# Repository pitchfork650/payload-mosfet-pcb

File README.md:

## backup-payload

# Welcome to the 2027 backup payload team!  

# Competition Objective:  
We need to drop a 3lb (1.36kg), 11in x 9in x 4in (280mm x 230mm x 102mm) object from a height of >=150ft above the ground within a 100ft diameter circle on the ground.  

The object must land intact and cannot free-fall!

# Design Priorities:

1: Reliability and Simplicity - This is the fallback plan and cannot fail!  
2: Aerodynamics - We cannot add excessive drag to the airframe.  
3: Weight - We are trying to stay under a total airframe weight of 18lb (8.16kg).  
4: Power - We cannot draw excessive amounts of power for our system.  

# Current Design:

We are going for a design based on a jet fighter drop tank design, with a blunter tip as we are not traveling supersonic.

- Electromagnetic release system (energize to release)
- Parachute retardant mechanism
- Completely unguided

# Documentation, Communication, and Files

We will keep as much documentation as possible in this Github, once we figure out how to use it.

Primary communication regarding meetings (not meeting notes) will be in the #backup-payload Discord channel in the TritonUAS Discord. 

- If you are having trouble finding the channel, go to your settings for the TritonUAS Discord server and find the "Show All Channels" toggle, and toggle it on.
- The channel is under the Electrical channel category.

Onshape document for all unguided payload models:
https://cad.onshape.com/documents/280ab2b1f08f9e136f51cc77/w/917fb5350924a7544787e597/e/dabe9ec72733b0c074b43efb?renderMode=0&uiState=6aeeb632a85a72a918cc2794 

Google document meeting notes (we are moving away from this ASAP): 
https://docs.google.com/document/d/1v5xJ7Shg4Nnc_SfwMuAoo-l7Iq7nKODf18gR5z6Hjh0/edit?usp=sharing
<!--
Gavin why

-->

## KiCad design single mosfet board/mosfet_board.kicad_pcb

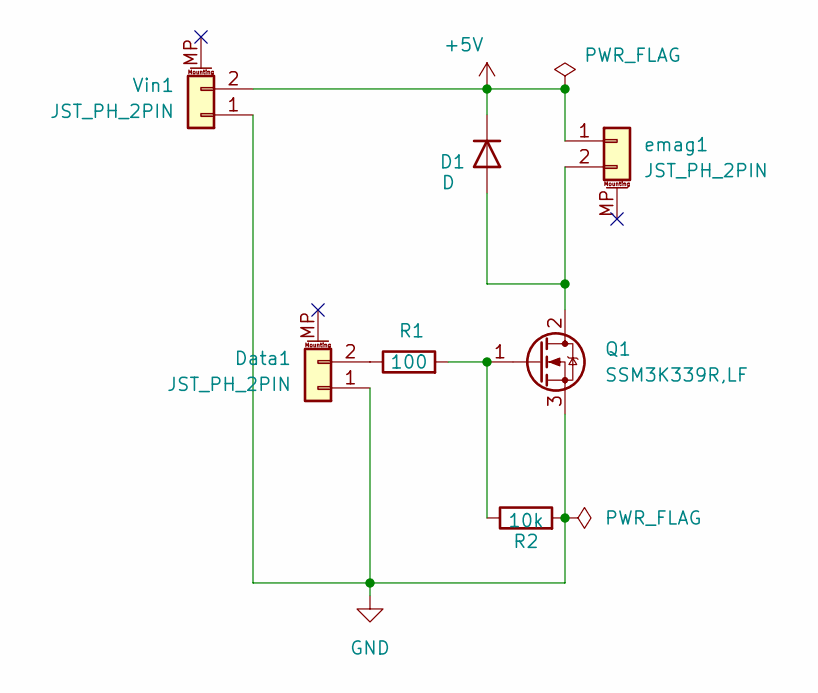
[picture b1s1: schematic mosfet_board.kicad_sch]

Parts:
D1: D; D_SOD-123
Data1: JST_PH_2PIN; JST_PH_S2B-PH-SM4-TB_1x02-1MP_P2.00mm_Horizontal
Q1: SSM3K339R,LF; SOT-23_Handsoldering
R1: 100; R_0603_1608Metric_Pad0.98x0.95mm_HandSolder
R2: 10k; R_0603_1608Metric_Pad0.98x0.95mm_HandSolder
Vin1: JST_PH_2PIN; JST_PH_S2B-PH-SM4-TB_1x02-1MP_P2.00mm_Horizontal
emag1: JST_PH_2PIN; JST_PH_S2B-PH-SM4-TB_1x02-1MP_P2.00mm_Horizontal

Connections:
+5V: D1.1 (K), Vin1.2, emag1.1
GND: Data1.1, Q1.3 (S), R2.2, Vin1.1
unnamed: D1.2 (A), Q1.2 (D), emag1.2
unnamed: Data1.2, R1.1
unnamed: Q1.1 (G), R1.2, R2.1

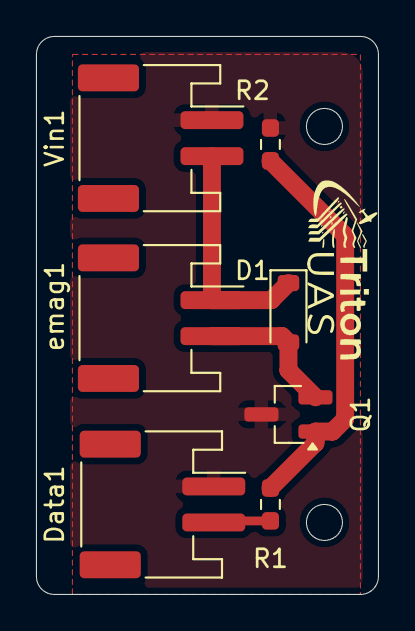
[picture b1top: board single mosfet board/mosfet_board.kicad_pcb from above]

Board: 2 copper layers, 19.0 x 31.0 mm, 7 parts (0 on the bottom side), 5 nets.

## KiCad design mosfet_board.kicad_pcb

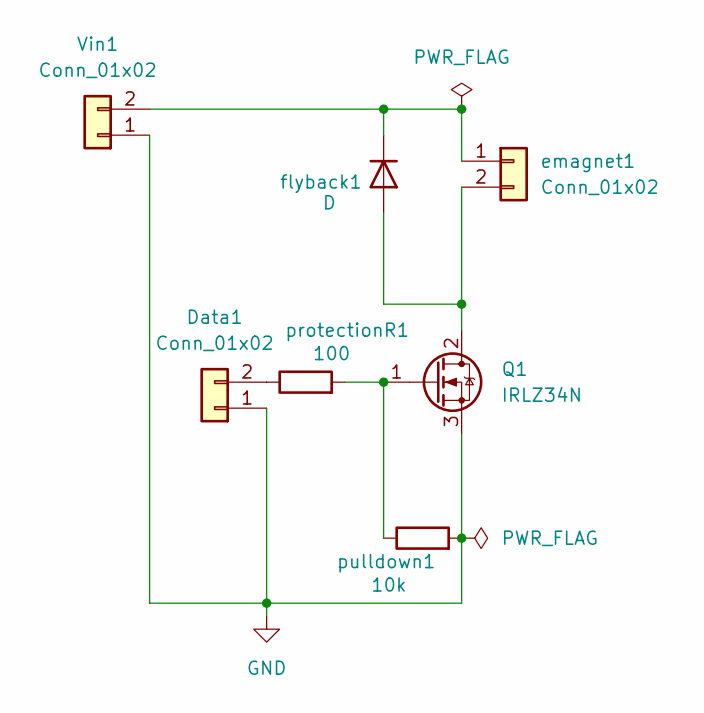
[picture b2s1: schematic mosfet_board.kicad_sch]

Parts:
Data1: Conn_01x02; JST_XH_S2B-XH-A_1x02_P2.50mm_Horizontal
Q1: IRLZ34N; TO-220-3_Vertical
Vin1: Conn_01x02; JST_XH_S2B-XH-A_1x02_P2.50mm_Horizontal
emagnet1: Conn_01x02; JST_XH_S2B-XH-A_1x02_P2.50mm_Horizontal
flyback1: D; D_DO-15_P10.16mm_Horizontal
protectionR1: 100; R_Axial_DIN0207_L6.3mm_D2.5mm_P10.16mm_Horizontal
pulldown1: 10k; R_Axial_DIN0207_L6.3mm_D2.5mm_P10.16mm_Horizontal

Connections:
GND: Data1.1, Q1.3 (S), Vin1.1, pulldown1.2
unnamed: Data1.2, protectionR1.1
unnamed: Q1.2 (D), emagnet1.2, flyback1.2 (A)
unnamed: Q1.1 (G), protectionR1.2, pulldown1.1
unnamed: Vin1.2, emagnet1.1, flyback1.1 (K)

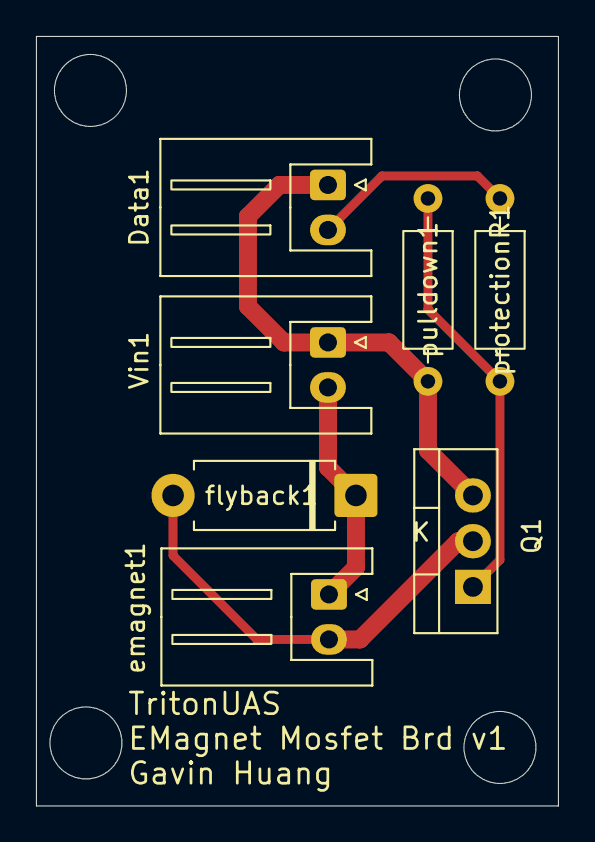
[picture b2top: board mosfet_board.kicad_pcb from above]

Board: 2 copper layers, 29.0 x 42.8 mm, 7 parts (0 on the bottom side), 5 nets.

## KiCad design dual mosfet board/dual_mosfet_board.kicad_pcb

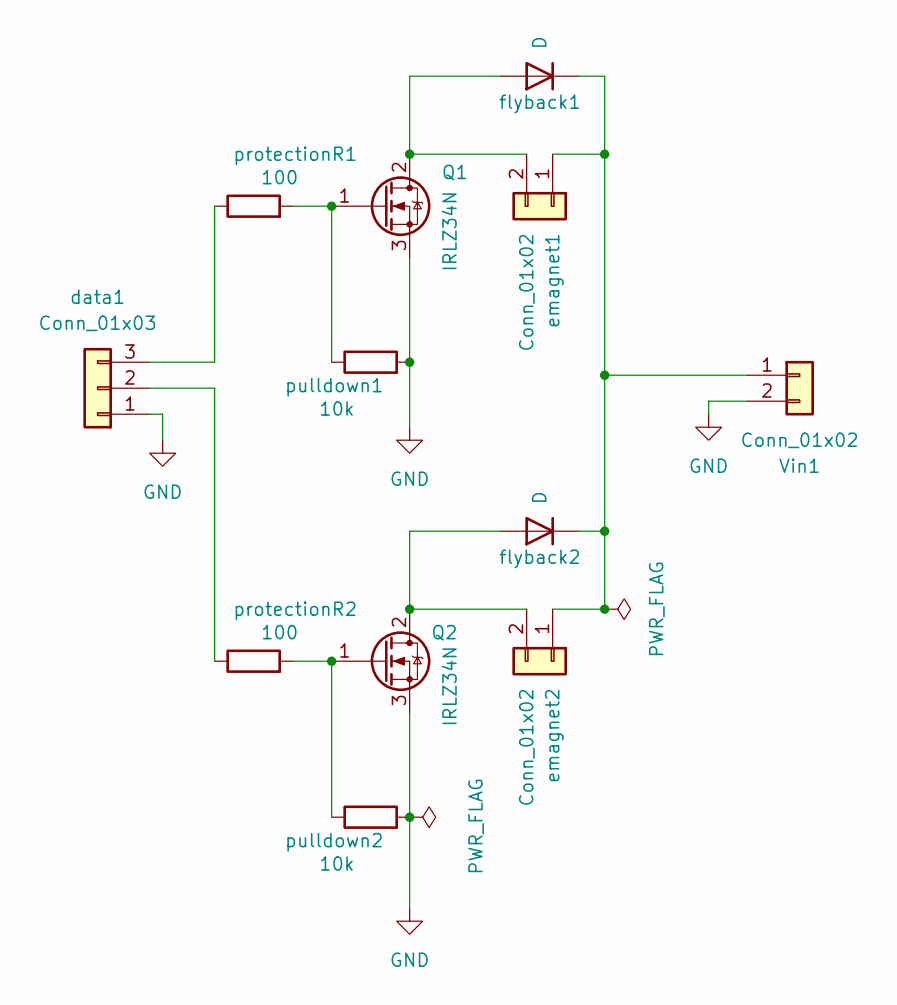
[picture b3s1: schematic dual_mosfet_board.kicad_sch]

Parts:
Q1, Q2: IRLZ34N; TO-220-3_Vertical
Vin1: Conn_01x02; JST_XH_S2B-XH-A_1x02_P2.50mm_Horizontal
data1: Conn_01x03; JST_XH_S3B-XH-A_1x03_P2.50mm_Horizontal
emagnet1, emagnet2: Conn_01x02; JST_XH_S2B-XH-A_1x02_P2.50mm_Horizontal
flyback1, flyback2: D; D_DO-15_P10.16mm_Horizontal
protectionR1, protectionR2: 100; R_Axial_DIN0207_L6.3mm_D2.5mm_P10.16mm_Horizontal
pulldown1, pulldown2: 10k; R_Axial_DIN0207_L6.3mm_D2.5mm_P10.16mm_Horizontal

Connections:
GND: Q1.3 (S), Q2.3 (S), Vin1.2, data1.1, pulldown1.2, pulldown2.2
unnamed: Q1.2 (D), emagnet1.2, flyback1.2 (A)
unnamed: Q1.1 (G), protectionR1.2, pulldown1.1
unnamed: Q2.2 (D), emagnet2.2, flyback2.2 (A)
unnamed: Q2.1 (G), protectionR2.2, pulldown2.1
unnamed: Vin1.1, emagnet1.1, emagnet2.1, flyback1.1 (K), flyback2.1 (K)
unnamed: data1.2, protectionR2.1
unnamed: data1.3, protectionR1.1

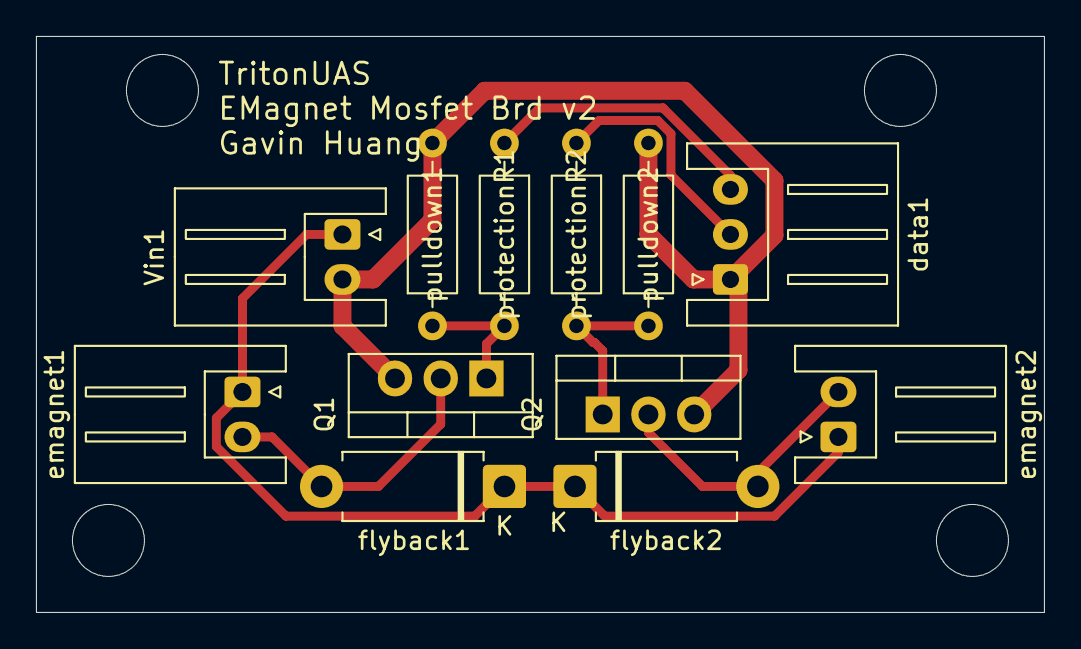
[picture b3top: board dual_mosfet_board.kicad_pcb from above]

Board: 2 copper layers, 56.0 x 32.0 mm, 12 parts (0 on the bottom side), 8 nets.
